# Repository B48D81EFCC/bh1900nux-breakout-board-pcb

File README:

# BH1900NUX Breakout Board
*KiCad project files for a breakout board using the Rohm Semiconductor BH1900NUX temperature sensor.*

## Overview
The BH1900NUX breakout board simplifies integration of the **BH1900NUX sensor** into your projects.  
The main goal of this PCB is to fit into stainless steel sleeve of around 5mm diameter.  

### Features
-  **A1 pin** Supported (solder jumper on the back)
- **A2 pin** Supported (solder jumper on the back)
- **A3 pin** Supported (solder jumper on the back)
- **ALERT pin** NOT supported (Pin is not exposed on the PCB)

### JST SH connector pinout

| Pin # | Function |
|-------|----------|
| 1     | GND      |
| 2     | 3.3V     |
| 3     | SDA      |
| 4     | SCL      |

The pinout layout is widely used across different vendors of breakout boards with JST SH connector, allowing to use multiple different sensors on one bus more easily. Although the pin layout is (often) the same, each vendor uses their own brand names (e.g: STEMMA, μŠup)

> [!CAUTION]
> The design is not 5V compliant and 5V will destroy the sensor.  
> **Use 3.3V only.** 

---

*Figure: BH1900NUX sensor breakout board front view (Rohm Semiconductor)*

*Figure: BH1900NUX sensor breakout board front view (Rohm Semiconductor)*

*Figure: BH1900NUX sensor breakout board back view (Rohm Semiconductor)*

*Figure: BH1900NUX sensor breakout board back view (Rohm Semiconductor)*

# Additional resources
[Official BH1900NUX Product Page (ROHM Website)](https://www.rohm.com/products/sensors-mems/temperature-sensor-ics/bh1900nux-product)

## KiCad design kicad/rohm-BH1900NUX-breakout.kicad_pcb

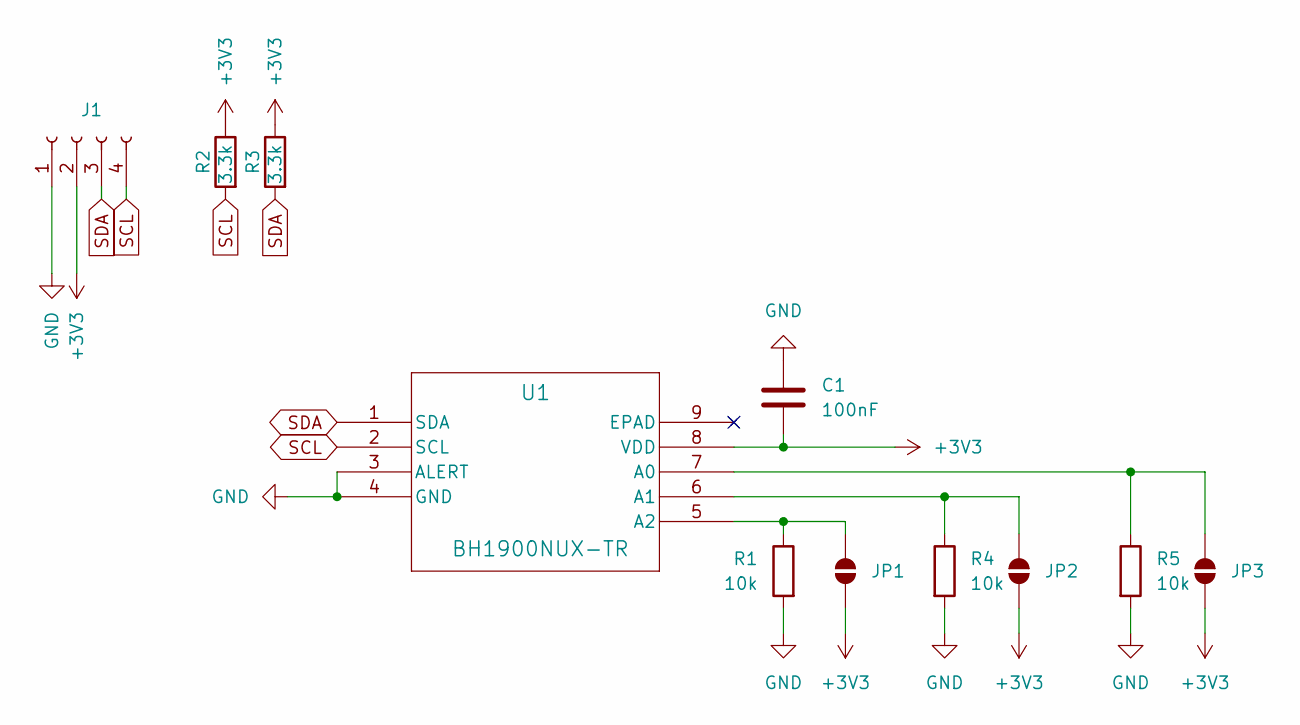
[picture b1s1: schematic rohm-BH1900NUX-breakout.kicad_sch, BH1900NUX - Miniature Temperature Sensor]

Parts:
C1: 100nF; C_01005_0402Metric
J1: Conn_01x04_Socket; JST_SH_SM04B-SRSS-TB_1x04-1MP_P1.00mm_Horizontal
JP1, JP2, JP3: Jumper_2_Small_Open; SolderJumper-2_P1.3mm_Open_Pad1.0x1.5mm
R1, R4, R5: 10k; R_01005_0402Metric
R2, R3: 3.3k; R_01005_0402Metric
U1: BH1900NUX-TR; VSON008X2030_ROM

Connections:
+3V3: C1.2, J1.2, JP1.2 (B), JP2.1 (A), JP3.1 (A), R2.1, R3.1, U1.8 (VDD)
GND: C1.1, J1.1, R1.2, R4.2, R5.2, U1.3 (ALERT), U1.4 (GND)
unnamed: JP1.1 (A), R1.1, U1.5 (A2)
unnamed: JP2.2 (B), R4.1, U1.6 (A1)
unnamed: JP3.2 (B), R5.1, U1.7 (A0)
SCL: J1.4, R2.2, U1.2 (SCL)
SDA: J1.3, R3.2, U1.1 (SDA)

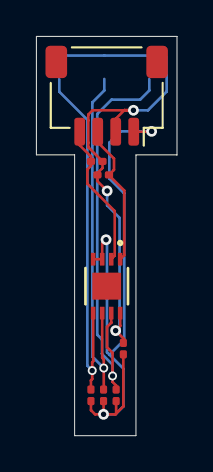
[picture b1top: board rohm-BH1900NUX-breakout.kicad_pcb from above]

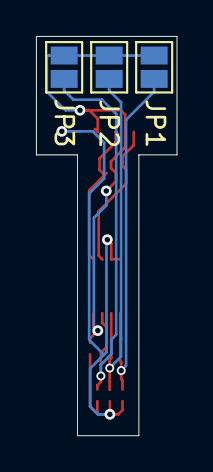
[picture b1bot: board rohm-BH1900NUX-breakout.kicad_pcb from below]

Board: 2 copper layers, 7.8 x 22.2 mm, 11 parts (3 on the bottom side), 7 nets.

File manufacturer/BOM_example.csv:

"Id";"Designator";"Footprint";"Quantity";"Designation";"Supplier and ref";
1;"R1,R4,R5";"R_0201_0603Metric";3;"10k";;;
2;"R3,R2";"R_0201_0603Metric";2;"3.3k";;;
3;"J1";"JST_SH_SM04B-SRSS-TB_1x04-1MP_P1.00mm_Horizontal";1;"Conn_01x04_Socket";;;
4;"U1";"VSON008X2030_ROM";1;"BH1900NUX-TR";;;
5;"C1";"C_0201_0603Metric";1;"100nF";;;

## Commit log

2025-11-09 Init
2025-11-09 Renamed README to README.md
2025-11-20 Layout updated
2026-01-13 Final schematics and final layout
2026-01-14 Readme updated. BOM file added
2026-01-14 Added some PCB photos
2026-01-14 Photos resized
2026-01-14 README updated
2026-01-16 New project structure
